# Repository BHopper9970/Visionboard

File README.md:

A WIP Radxa CM5 based IO board for vision systems

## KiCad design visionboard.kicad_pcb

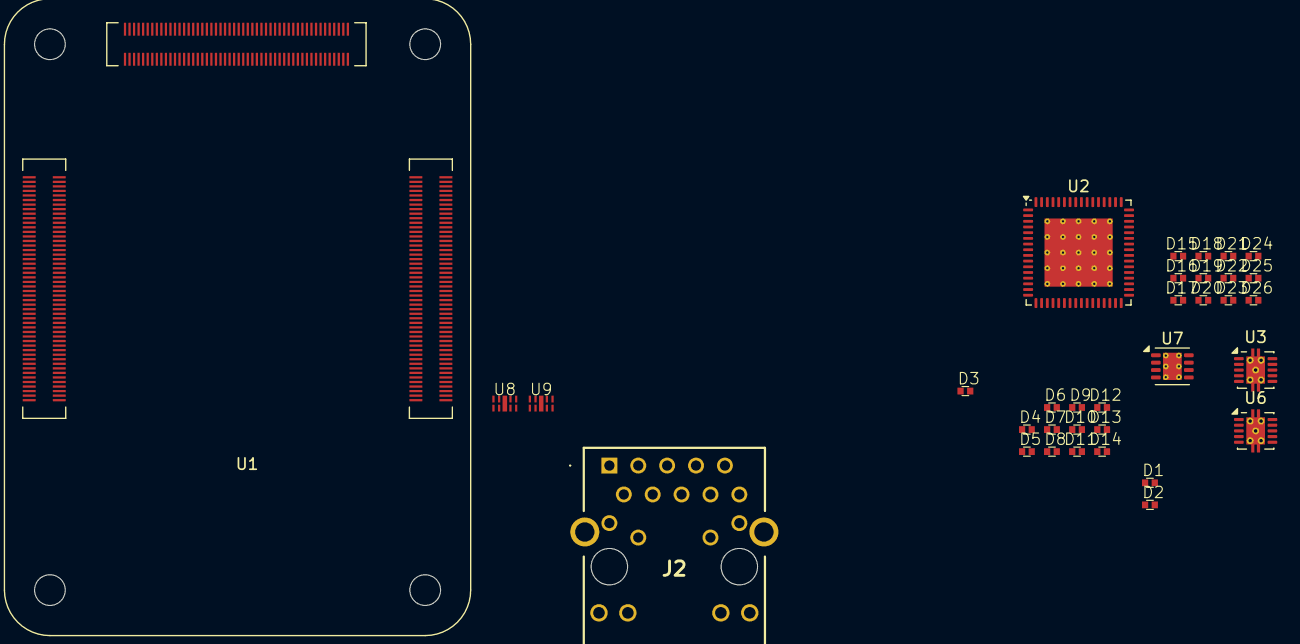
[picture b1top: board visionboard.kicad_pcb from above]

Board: 2 copper layers, 34 parts (0 on the bottom side), 36 nets, no tracks yet.

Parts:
D1, D2, D3, D4, D5, D6, D7, D8, D9, D10, D11, D12, D13, D14, D15, D16, D17, D18, D19, D20, D21, D22, D23, D24, D25, D26: ESD5311N-2/TR; DFN1006-2L
J2: LPJG0926HENL
U1: Hirose DF40C-100DS-0.4V; Radxa_CM5
U2: TUSB8041IPAPQ1; QFN-64-1EP_9x9mm_P0.5mm_EP6x6mm_ThermalVias
U3, U6: TPS2561; VSON-10-1EP_3x3mm_P0.5mm_EP1.65x2.4mm_ThermalVias
U7: TPS74611PQWDRBRQ1; VSON-8-1EP_3x3mm_P0.65mm_EP1.65x2.4mm_ThermalVias
U8, U9: ESD5344-D

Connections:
+1.8v_(Output): U1.88 (+1.8v_(Output)), U1.90 (+1.8v_(Output)), U7.5 (EN), U7.8 (IN)
+3.3v_(Output): U1.84 (+3.3v_(Output)), U1.86 (+3.3v_(Output))
+5v_(Input): U1.77 (+5v_(Input)), U1.79 (+5v_(Input)), U1.81 (+5v_(Input)), U1.83 (+5v_(Input)), U1.85 (+5v_(Input)), U1.87 (+5v_(Input))
/USB3/USB3down12/USB_SSRXM_DN1: D3.1 (A1), U2.39 (USB_SSRXM_DN1)
/USB3/USB3down12/USB_SSRXM_DN2: D9.1 (A1), U2.47 (USB_SSRXM_DN2)
/USB3/USB3down12/USB_SSRXP_DN1: D4.1 (A1), U2.38 (USB_SSRXP_DN1)
/USB3/USB3down12/USB_SSRXP_DN2: D10.1 (A1), U2.46 (USB_SSRXP_DN2)
/USB3/USB3down34/USB_SSRXM_DN3: D20.1 (A1), U2.55 (USB_SSRXM_DN3)
/USB3/USB3down34/USB_SSRXM_DN4: D15.1 (A1), U2.62 (USB_SSRXM_DN4)
/USB3/USB3down34/USB_SSRXP_DN3: D22.1 (A1), U2.54 (USB_SSRXP_DN3)
/USB3/USB3down34/USB_SSRXP_DN4: D16.1 (A1), U2.61 (USB_SSRXP_DN4)
/USB3/USB3pwr/VDD: U2.19 (VDD), U2.25 (VDD), U2.37 (VDD), U2.45 (VDD), U2.53 (VDD), U2.60 (VDD), U2.63 (VDD)
/USB3/USB3pwr/VDD33: U2.2 (VDD33), U2.20 (VDD33), U2.31 (VDD33), U2.48 (VDD33)
/USB3/USB3sw/OVERCUR1Z: U2.14 (OVERCUR1z), U3.10 (~FAULT1)
/USB3/USB3sw/OVERCUR2Z: U2.15 (OVERCUR2z), U3.6 (~FAULT2)
/USB3/USB3sw/OVERCUR3Z: U2.12 (OVERCUR3z), U6.10 (~FAULT1)
/USB3/USB3sw/OVERCUR4Z: U2.11 (OVERCUR4z), U6.6 (~FAULT2)
/USB3/USB3sw/PWRCTRL1_BATEN1: U2.4 (PWRCTL1/BATEN1), U3.4 (EN1)
/USB3/USB3sw/PWRCTRL2_BATEN2: U2.3 (PWRCTL2/BATEN2), U3.5 (EN2)
/USB3/USB3sw/PWRCTRL3_BATEN3: U2.1 (PWRCTL3/BATEN3), U6.4 (EN1)
/USB3/USB3sw/PWRCTRL4_BATEN4: U2.64 (PWRCTL4/BATEN4), U6.5 (EN2)
Ethernet_Pair0_N: J2.2 (TD1-), U1.10 (Ethernet_Pair0_N), U8.9 (NC9)
Ethernet_Pair0_P: J2.1 (TD1+), U1.12 (Ethernet_Pair0_P), U8.1 (IO1), U8.10 (NC10)
Ethernet_Pair1_N: J2.4 (TD2-_1), U1.6 (Ethernet_Pair1_N), U8.5 (IO4), U8.6 (NC6)
Ethernet_Pair1_P: J2.3 (TD2+), U1.4 (Ethernet_Pair1_P), U8.4 (IO3), U8.7 (NC7)
Ethernet_Pair2_N: J2.8 (TD3-), U1.9 (Ethernet_Pair2_N), U9.9 (NC9)
Ethernet_Pair2_P: J2.7 (TD3+), U1.11 (Ethernet_Pair2_P), U9.1 (IO1), U9.10 (NC10)
Ethernet_Pair3_N: J2.10 (TD4-), U1.5 (Ethernet_Pair3_N), U9.5 (IO4), U9.6 (NC6)
Ethernet_Pair3_P: J2.9 (TD4+), U1.3 (Ethernet_Pair3_P), U9.4 (IO3), U9.7 (NC7)
GND: D1.2 (A2), D2.2 (A2), D3.2 (A2), D4.2 (A2), D5.2 (A2), D6.2 (A2), D7.2 (A2), D8.2 (A2), D9.2 (A2), D10.2 (A2), D11.2 (A2), D12.2 (A2), D13.2 (A2), D14.2 (A2), D15.2 (A2), D16.2 (A2), D17.2 (A2), D18.2 (A2), D19.2 (A2), D20.2 (A2), D21.2 (A2), D22.2 (A2), D23.2 (A2), D24.2 (A2), D25.2 (A2), D26.2 (A2), J2.16 (K_GREEN), J2.18 (K_YELLOW), U1.1 (GND), U1.2 (GND), U1.7 (GND), U1.8 (GND), U1.13 (GND), U1.14 (GND), U1.22 (GND), U1.23 (GND), U1.32 (GND), U1.33 (GND), U1.42 (GND), U1.43 (GND), U1.52 (GND), U1.53 (GND), U1.59 (GND), U1.60 (GND), U1.65 (GND), U1.66 (GND), U1.71 (GND), U1.74 (GND), U1.98 (GND), U1.107 (GND), U1.108 (GND), U1.113 (GND), U1.114 (GND), U1.119 (GND), U1.120 (GND), U1.125 (GND), U1.126 (GND), U1.131 (GND), U1.132 (GND), U1.137 (GND), U1.138 (GND), U1.144 (GND), U1.150 (GND), U1.155 (GND), U1.156 (GND), U1.161 (GND), U1.162 (GND), U1.167 (GND), U1.168 (GND), U1.173 (GND), U1.174 (GND), U1.179 (GND), U1.180 (GND), U1.185 (GND), U1.186 (GND), U1.191 (GND), U1.192 (GND), U1.197 (GND), U1.198 (GND), U1.201 (GND), U1.202 (GND), U1.207 (GND), U1.213 (GND), U1.219 (GND), U1.222 (GND), U1.225 (GND), U1.231 (GND), U1.232 (GND), U1.237 (GND), U1.242 (GND), U1.243 (GND), U1.248 (GND), U1.249 (GND), U1.255 (GND), U1.256 (GND), U1.261 (GND), U1.262 (GND), U1.267 (GND), U1.268 (GND), U1.272 (GND), U1.273 (GND), U1.276 (GND), U1.299 (GND), U1.300 (GND), U2.65 (VSS), U3.1 (GND), U3.11 (PAD), U6.1 (GND), U6.11 (PAD), U7.4 (GND), U8.3 (GND), U8.8 (GND), U9.3 (GND), U9.8 (GND)
unnamed: J2.5 (TD2-_2), J2.6 (TD2-_3)
USB3_HOST1_DM: U1.247 (USB3_HOST1_DM), U2.22 (USB_DM_UP)
USB3_HOST1_DP: U1.245 (USB3_HOST1_DP), U2.21 (USB_DP_UP)
USB3_HOST1_SSRXN: U1.259 (USB3_HOST1_SSRXN), U2.27 (USB_SSRXM_UP)
USB3_HOST1_SSRXP: U1.257 (USB3_HOST1_SSRXP), U2.26 (USB_SSRXP_UP)
VCC5V0_USB: U3.2 (IN), U3.3 (IN), U6.2 (IN), U6.3 (IN)

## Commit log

2025-10-01 added CM5 footprint
2025-10-01 microSD card
2025-10-11 removed SD card, began usb work
2025-10-11 usb work cont
2025-10-11 removed SD schematic
2025-10-11 net defs
2025-10-14 finished USB 2.0
2025-10-14 usb2 fixes and usb3 started
2025-10-14 usb3 work cont
2025-10-14 added radxa documentation
2025-10-14 added power page
2025-10-15 usb3up done, usb3down begun
2025-10-15 usb3 down done
2025-10-17 finished usb3.0
2025-10-18 Ethernet and MIPI cam done, USBC OTG started
2025-10-19 usbc work
2025-10-20 usbc done, replaced pcb with radxa example
2025-10-21 sysinfo started, usbc done?
